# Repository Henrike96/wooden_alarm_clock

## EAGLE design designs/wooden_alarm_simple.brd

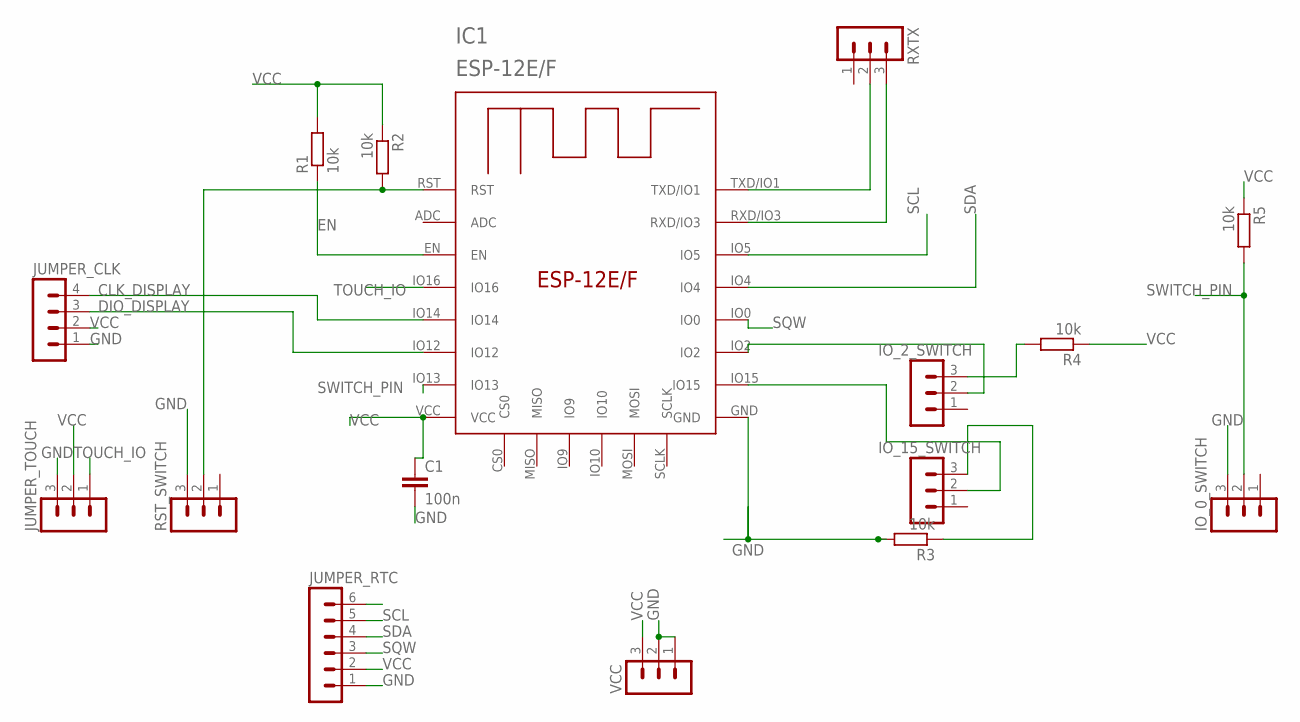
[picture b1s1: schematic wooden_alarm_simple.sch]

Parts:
C1: 100n; C0805
IC1: ESP-12E/F; ESP-12E
IO_0_SWITCH, IO_2_SWITCH, IO_15_SWITCH: MA03-1
JUMPER_CLK: MA04-1
JUMPER_RTC: MA06-1
JUMPER_TOUCH: MA03-1
R1, R2, R3, R4, R5: 10k; R0805
RST_SWITCH: MA03-1
RXTX: MA03-1
VCC: MA03-1

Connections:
CLK_DISPLAY: IC1.IO14, JUMPER_CLK.4
DIO_DISPLAY: IC1.IO12, JUMPER_CLK.3
EN: IC1.EN, R1.1
GND: C1.2, IC1.GND, IO_0_SWITCH.3, JUMPER_CLK.1, JUMPER_RTC.1, JUMPER_TOUCH.3, R3.2, RST_SWITCH.3, VCC.1, VCC.2
unnamed: IC1.RST, R2.2, RST_SWITCH.2
unnamed: IO_2_SWITCH.3, R4.2
unnamed: IC1.IO15, IO_15_SWITCH.2
unnamed: IO_15_SWITCH.3, R3.1
unnamed: IC1.IO2, IO_2_SWITCH.2
RX: IC1.RXD/IO3, RXTX.3
SCL: IC1.IO5, JUMPER_RTC.5
SDA: IC1.IO4, JUMPER_RTC.4
SQW: IC1.IO0, JUMPER_RTC.3
SWITCH_PIN: IC1.IO13, IO_0_SWITCH.2, R5.2
TOUCH_IO: IC1.IO16, JUMPER_TOUCH.1
TX: IC1.TXD/IO1, RXTX.2
VCC: C1.1, IC1.VCC, JUMPER_CLK.2, JUMPER_RTC.2, JUMPER_TOUCH.2, R1.2, R2.1, R4.1, R5.1, VCC.3

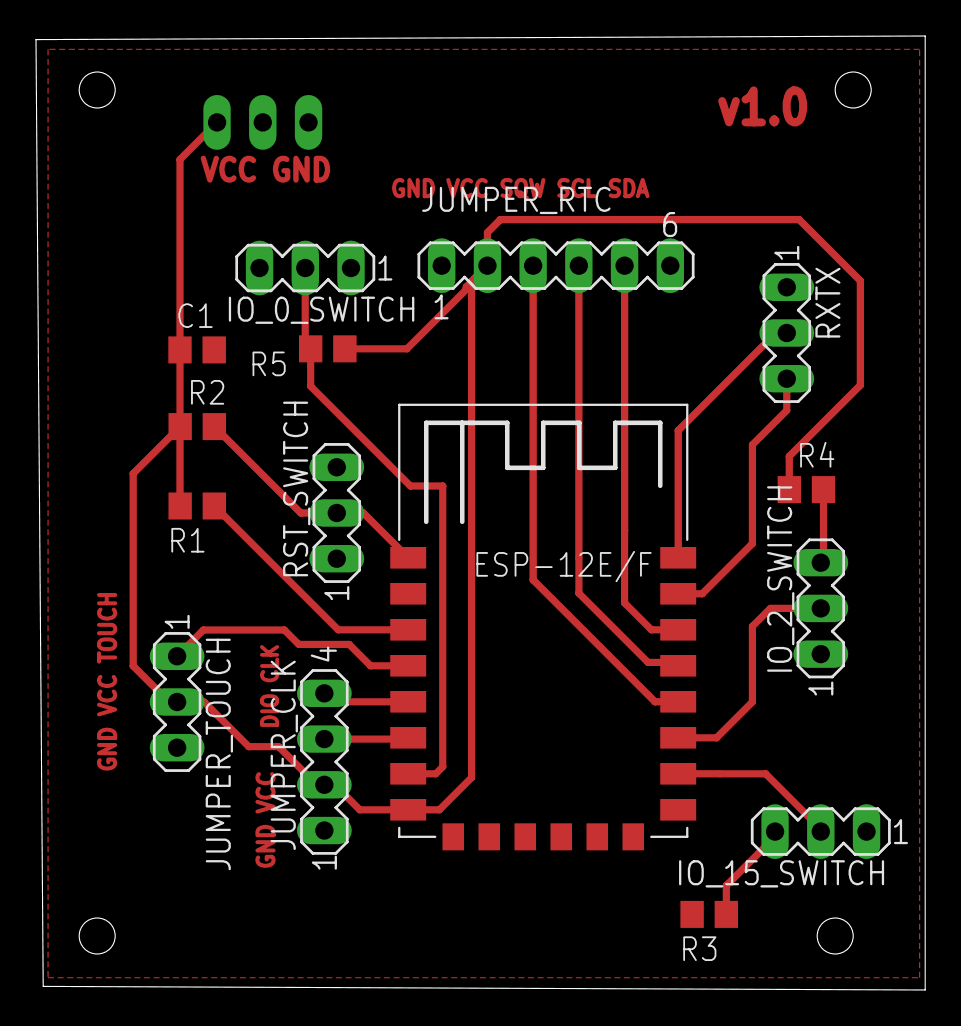
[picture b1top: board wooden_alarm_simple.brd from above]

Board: 2 copper layers, 49.4 x 53.0 mm, 16 parts (1 on the bottom side), 17 nets.

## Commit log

2022-03-14 initial commit for alarm clock. Alarm not working yet.
2022-03-19 pw shift
2022-03-19 new design and dirs
2022-03-20 removed comment
2022-04-08 additions on software, alarm working, encoder working, copied folder
2022-04-08 removed commented stuff
2022-04-19 added eagle files
2022-04-19 changed designs
2022-05-09 add support for esp8826
2022-05-09 final changes v1 design
2022-05-09 added simpler design
2022-06-13 printready alarm simple layout
2022-06-13 pdf for pcb
2022-06-15 updated layout and pdf for etching
2022-06-30 working version, only touch
2022-06-30 fixed hour bug
2022-07-04 minor adaptions
